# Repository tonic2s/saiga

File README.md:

# Saiga Keyboard

A line of mechanical keyboards.
- [Prototyping Board](prototyping-board/README.md)
- [Keypad / Numpad](keypad/README.md)

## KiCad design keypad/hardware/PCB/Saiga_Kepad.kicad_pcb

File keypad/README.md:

# Saiga Keypad

A mechanical keypad.

## Features
- ISO keypad
- 17 mechanical switches
- 2 rotary encoder
- 3 plate mounted stabilizer
- Single color backlight
- RGB LED for each key
- Raspberry Pico as micro controler solderd on to the PCB
- [Driver in Circuit Python](driver/README.md)

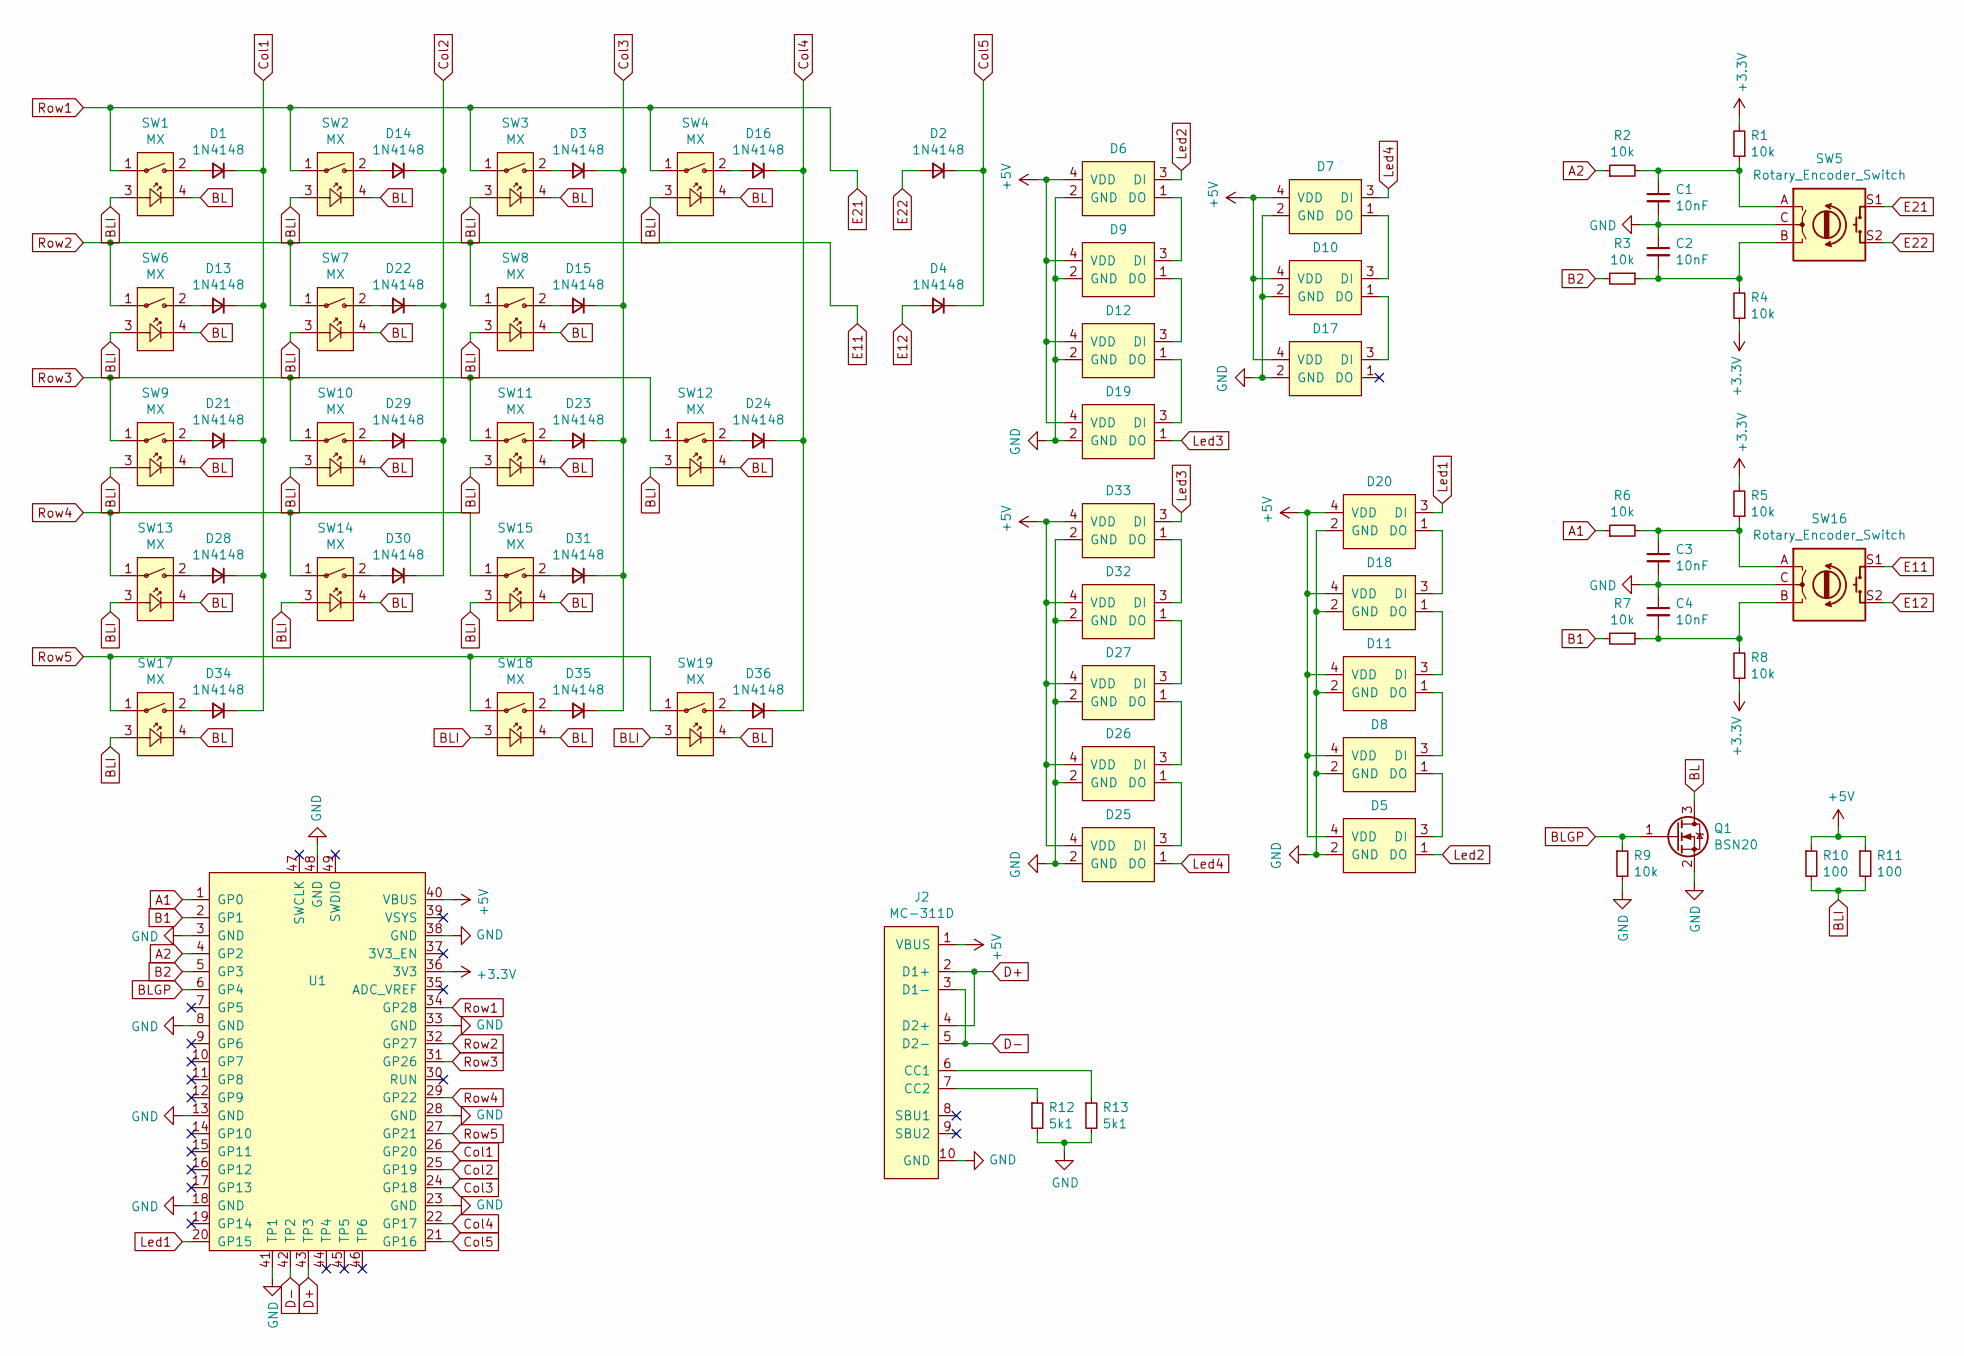
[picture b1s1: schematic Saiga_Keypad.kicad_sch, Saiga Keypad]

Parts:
C1, C2, C3, C4: 10nF; C_0805_2012Metric_Pad1.18x1.45mm_HandSolder
D1, D2, D3, D4, D13, D14, D15, D16, D21, D22, D23, D24, D28, D29, D30, D31, D34, D35, D36: 1N4148; D_SOD-123
D5, D6, D7, D8, D9, D10, D11, D12, D17, D18, D19, D20, D25, D26, D27, D32, D33: WS2812B-2020
J2: MC-311D
Q1: BSN20; SOT-23
R1, R2, R3, R4, R5, R6, R7, R8, R9: 10k; R_0805_2012Metric_Pad1.20x1.40mm_HandSolder
R10, R11: 100; R_2512_6332Metric_Pad1.40x3.35mm_HandSolder
R12, R13: 5k1; R_0805_2012Metric_Pad1.20x1.40mm_HandSolder
SW1, SW2, SW3, SW4, SW6, SW7, SW8, SW9, SW10, SW11, SW12, SW13, SW14, SW15, SW17, SW18, SW19: MX; Cherry_MX_5_Led
SW5, SW16: Rotary_Encoder_Switch; RotaryEncoder_Alps_EC12E-Switch_Vertical_H20mm_CircularMoun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
U1: RP2040_Pico; RP Pico

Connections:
+3V3: R1.2, R4.1, R5.2, R8.1, U1.36 (3V3)
+5V: D5.4 (VDD), D6.4 (VDD), D7.4 (VDD), D8.4 (VDD), D9.4 (VDD), D10.4 (VDD), D11.4 (VDD), D12.4 (VDD), D17.4 (VDD), D18.4 (VDD), D19.4 (VDD), D20.4 (VDD), D25.4 (VDD), D26.4 (VDD), D27.4 (VDD), D32.4 (VDD), D33.4 (VDD), J2.1 (VBUS), R10.1, R11.1, U1.40 (VBUS)
A1: R6.1, U1.1 (GP0)
A2: R2.1, U1.4 (GP2)
B1: R7.2, U1.2 (GP1)
B2: R3.2, U1.5 (GP3)
BL: Q1.3 (D), SW1.4, SW2.4, SW3.4, SW4.4, SW6.4, SW7.4, SW8.4, SW9.4, SW10.4, SW11.4, SW12.4, SW13.4, SW14.4, SW15.4, SW17.4, SW18.4, SW19.4
BLGP: Q1.1 (G), R9.1, U1.6 (GP4)
BLI: R10.2, R11.2, SW1.3, SW2.3, SW3.3, SW4.3, SW6.3, SW7.3, SW8.3, SW9.3, SW10.3, SW11.3, SW12.3, SW13.3, SW14.3, SW15.3, SW17.3, SW18.3, SW19.3
Col1: D1.1 (K), D13.1 (K), D21.1 (K), D28.1 (K), D34.1 (K), U1.26 (GP20)
Col2: D14.1 (K), D22.1 (K), D29.1 (K), D30.1 (K), U1.25 (GP19)
Col3: D3.1 (K), D15.1 (K), D23.1 (K), D31.1 (K), D35.1 (K), U1.24 (GP18)
Col4: D16.1 (K), D24.1 (K), D36.1 (K), U1.22 (GP17)
Col5: D2.1 (K), D4.1 (K), U1.21 (GP16)
D+: J2.2 (D1+), J2.4 (D2+), U1.43 (TP3)
D-: J2.3 (D1-), J2.5 (D2-), U1.42 (TP2)
E11: SW6.1, SW7.1, SW8.1, SW16.S1, U1.32 (GP27)
E12: D4.2 (A), SW16.S2
E21: SW1.1, SW2.1, SW3.1, SW4.1, SW5.S1, U1.34 (GP28)
E22: D2.2 (A), SW5.S2
GND: C1.2, C2.1, C3.2, C4.1, D5.2 (GND), D6.2 (GND), D7.2 (GND), D8.2 (GND), D9.2 (GND), D10.2 (GND), D11.2 (GND), D12.2 (GND), D17.2 (GND), D18.2 (GND), D19.2 (GND), D20.2 (GND), D25.2 (GND), D26.2 (GND), D27.2 (GND), D32.2 (GND), D33.2 (GND), J2.10 (GND), Q1.2 (S), R9.2, R12.2, R13.2, SW5.C, SW16.C, U1.3 (GND), U1.8 (GND), U1.13 (GND), U1.18 (GND), U1.23 (GND), U1.28 (GND), U1.33 (GND), U1.38 (GND), U1.41 (TP1), U1.48 (GND)
Led1: D20.3 (DI), U1.20 (GP15)
Led2: D5.1 (DO), D6.3 (DI)
Led3: D19.1 (DO), D33.3 (DI)
Led4: D7.3 (DI), D25.1 (DO)
unnamed: C1.1, R1.1, R2.2, SW5.A
unnamed: C2.2, R3.1, R4.2, SW5.B
unnamed: C3.1, R5.1, R6.2, SW16.A
unnamed: C4.2, R7.1, R8.2, SW16.B
unnamed: D1.2 (A), SW1.2
unnamed: D3.2 (A), SW3.2
unnamed: D5.3 (DI), D8.1 (DO)
unnamed: D6.1 (DO), D9.3 (DI)
unnamed: D10.1 (DO), D17.3 (DI)
unnamed: D7.1 (DO), D10.3 (DI)
unnamed: D8.3 (DI), D11.1 (DO)
unnamed: D11.3 (DI), D18.1 (DO)
unnamed: D12.1 (DO), D19.3 (DI)
unnamed: D9.1 (DO), D12.3 (DI)
unnamed: D13.2 (A), SW6.2
unnamed: D14.2 (A), SW2.2
unnamed: D15.2 (A), SW8.2
unnamed: D16.2 (A), SW4.2
unnamed: D18.3 (DI), D20.1 (DO)
unnamed: D21.2 (A), SW9.2
unnamed: D22.2 (A), SW7.2
unnamed: D23.2 (A), SW11.2
unnamed: D24.2 (A), SW12.2
unnamed: D25.3 (DI), D26.1 (DO)
unnamed: D26.3 (DI), D27.1 (DO)
unnamed: D27.3 (DI), D32.1 (DO)
unnamed: D28.2 (A), SW13.2
unnamed: D29.2 (A), SW10.2
unnamed: D30.2 (A), SW14.2
unnamed: D31.2 (A), SW15.2
unnamed: D32.3 (DI), D33.1 (DO)
unnamed: D34.2 (A), SW17.2
unnamed: D35.2 (A), SW18.2
unnamed: D36.2 (A), SW19.2
unnamed: J2.6 (CC1), R13.1
unnamed: J2.7 (CC2), R12.1
Row3: SW9.1, SW10.1, SW11.1, SW12.1, U1.31 (GP26)
Row4: SW13.1, SW14.1, SW15.1, U1.29 (GP22)
Row5: SW17.1, SW18.1, SW19.1, U1.27 (GP21)

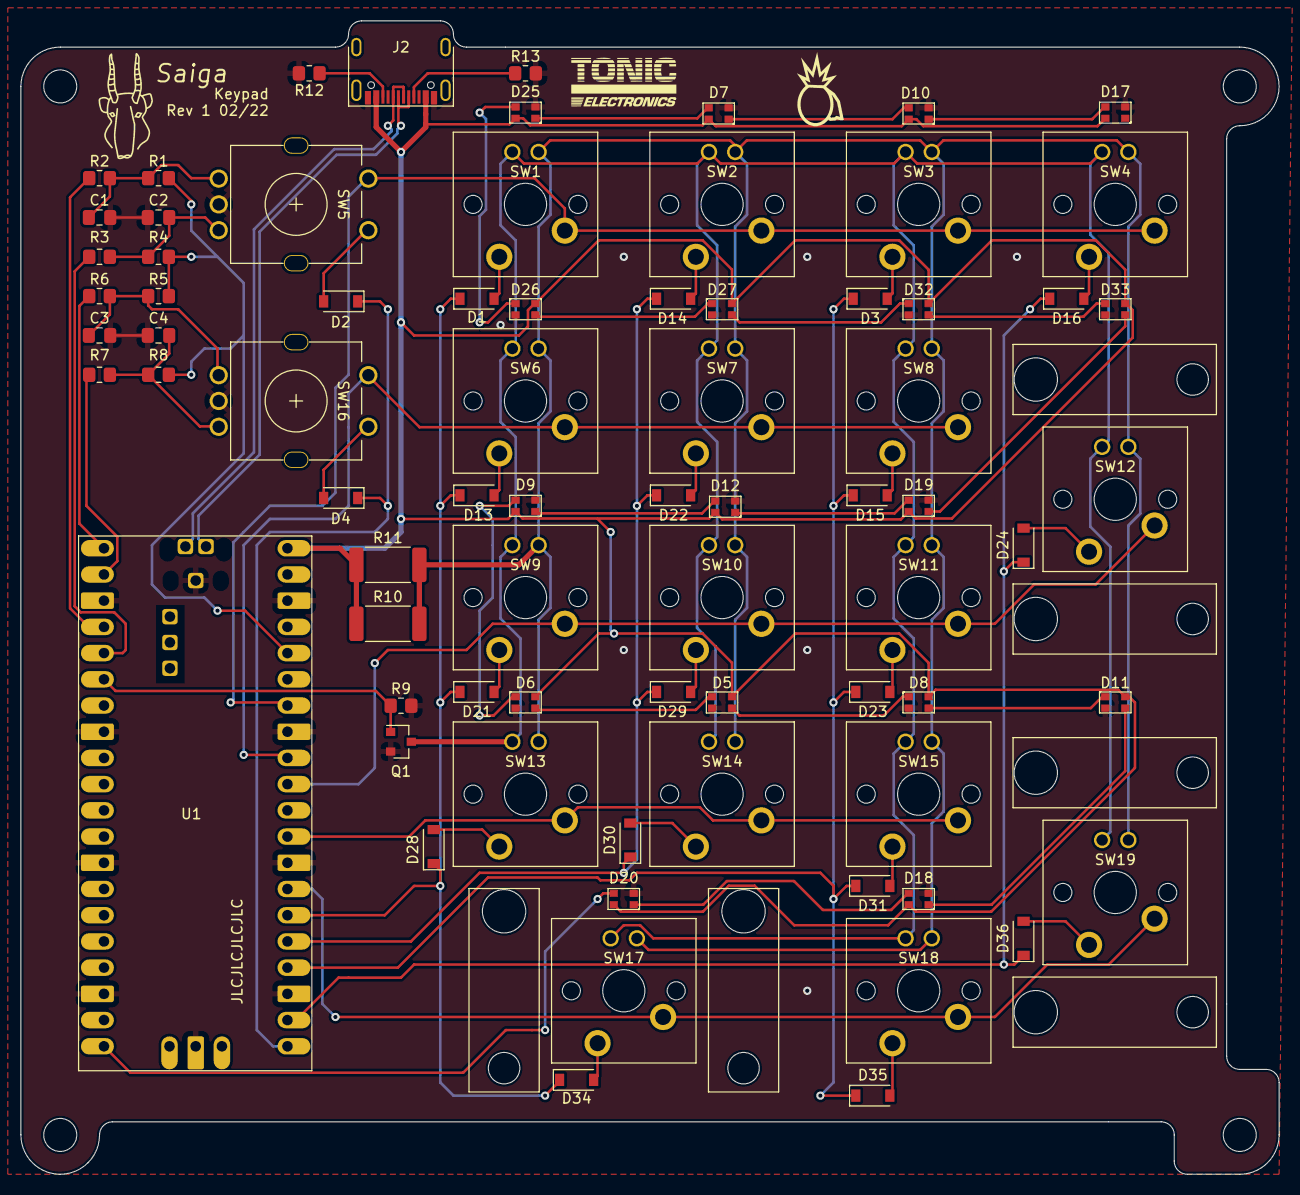
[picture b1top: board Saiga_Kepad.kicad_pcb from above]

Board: 2 copper layers, 121.9 x 111.8 mm, 75 parts (0 on the bottom side), 64 nets.

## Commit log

2021-10-16 Add initial README's, logo and existing file for prototyping board
2022-02-18 Remove watchdog
2022-02-18 WIP: Rework driver to use a scheduler for parallel processing
2022-02-19 initial upload of kicad files
    Added kicad schematic and kicad pcb
2022-02-19 Added README
2022-02-19 Added gerber files
2022-02-19 Make folders lowercase, copy driver and add readme
2022-02-20 WIP: Update keypad driver
2022-02-23 First working keypad driver release
2022-02-25 Add message bus to the keypad driver and use async module to check keys
2022-02-27 added Case
2022-02-27 Switch to asyncio scheduling and make consumer only react to commands
2022-02-27 Separate lighting into multiple programs sharing the NeoPixels
2022-02-27 Remove outdated imports
2022-02-28 added animations, implemented pulse animation, minor bug fix with timed tasks
2022-03-01 Make a command bus out of the message bus and rename modules
2022-04-24 Add generic AbstractInputHandler, ActionMap's and basic actions - Support for HID Consumer Control codes
2022-04-24 Add modifier helper actions
2022-04-25 Add mouse action support
2022-04-25 Add support for action layer switching
2022-04-25 Add support for midi actions
2022-04-26 Add more MIDI controller including variable modulation
2022-04-26 Refactor lighting system and choose unified names for commands
2022-04-29 Unify AbstractAction and AbstractLayerAction to a combined interface
2022-04-29 Add LayerCycleAction and only differentiate up and down for change image
2022-04-29 Add two class diagrams of the keypad driver
2022-04-29 Add rendered PlantUML diagrams to driver readme
2022-04-29 Add dependency's to readme
